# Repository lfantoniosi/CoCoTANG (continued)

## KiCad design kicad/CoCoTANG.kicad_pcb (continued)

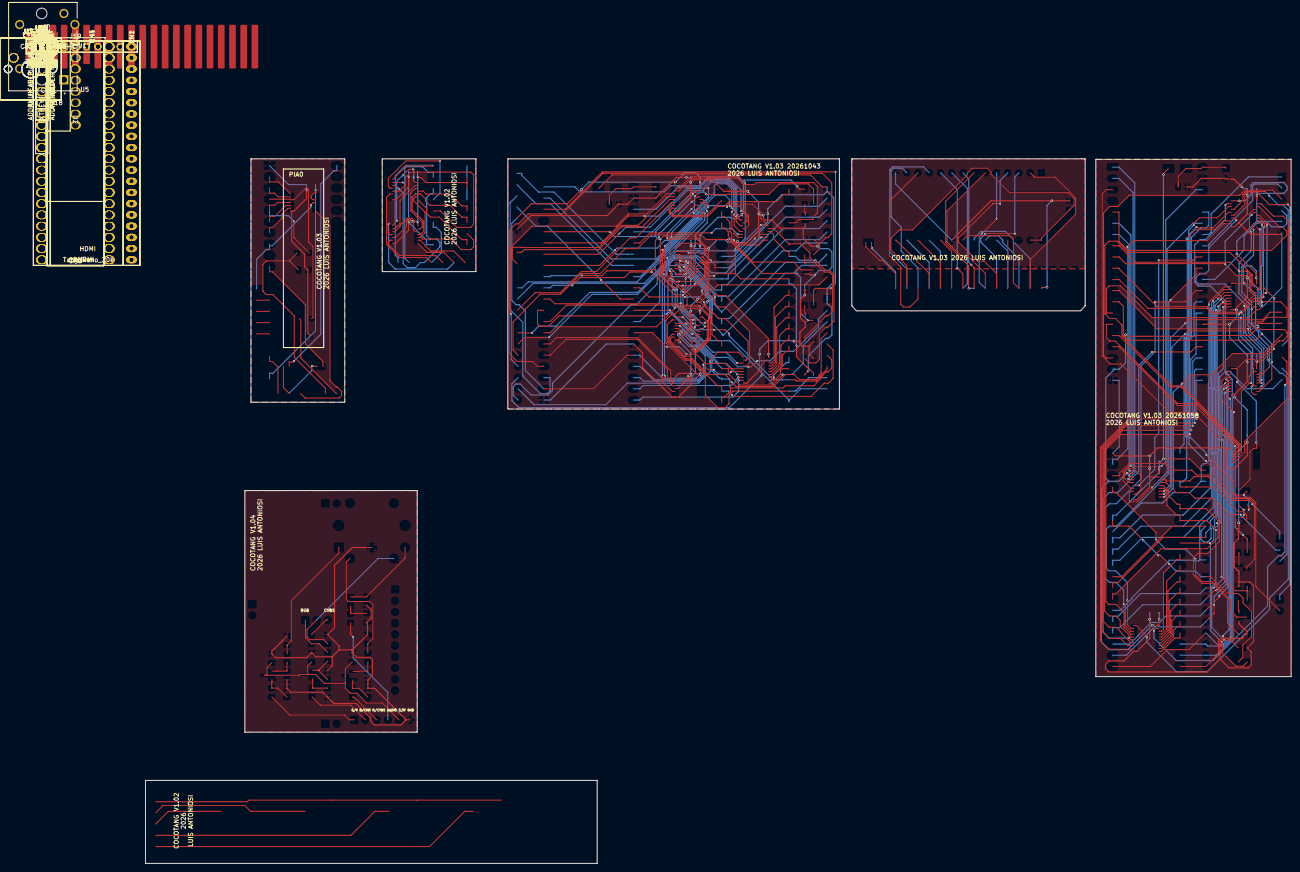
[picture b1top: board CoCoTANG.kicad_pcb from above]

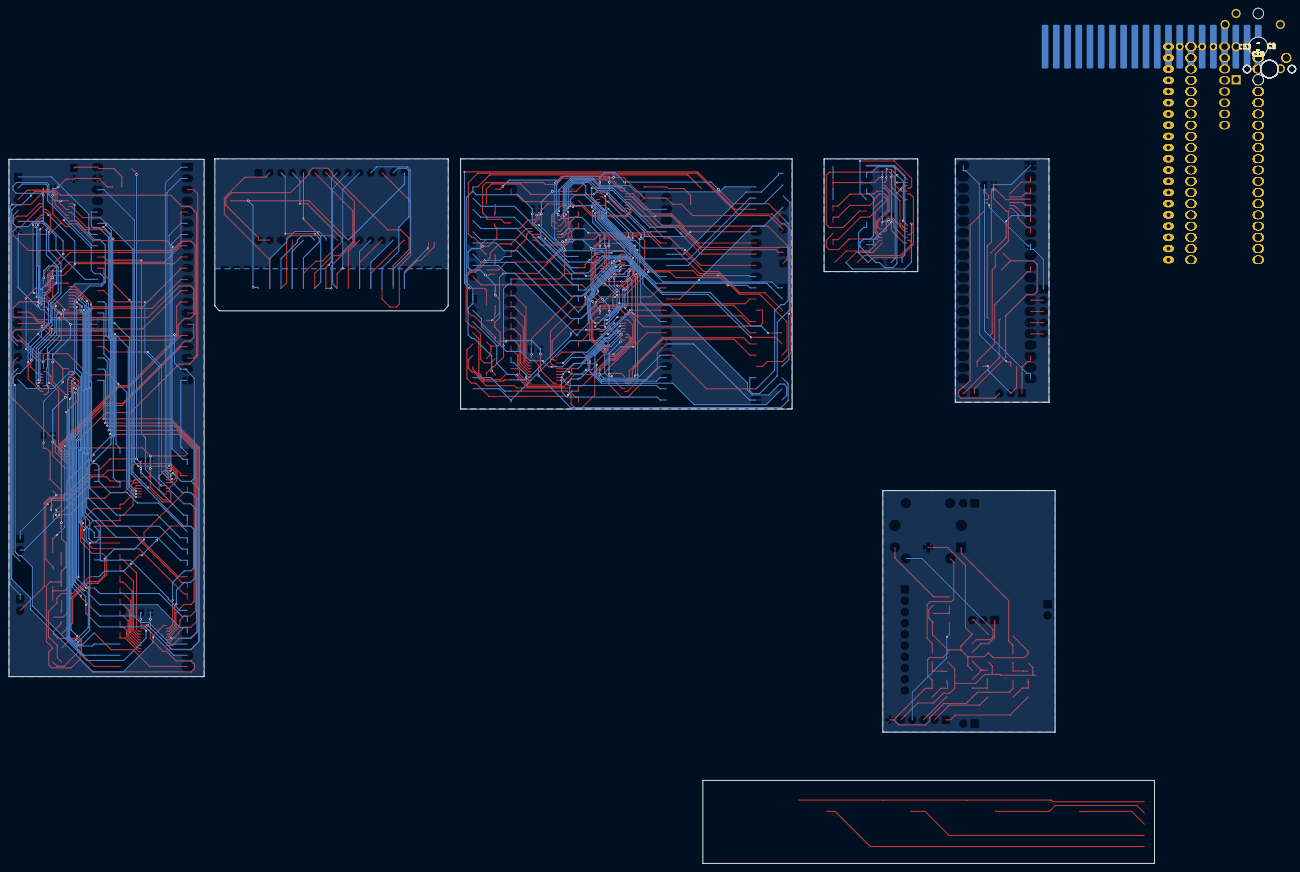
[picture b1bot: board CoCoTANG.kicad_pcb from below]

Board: 2 copper layers, 259.3 x 159.5 mm, 131 parts (15 on the bottom side), 129 nets.

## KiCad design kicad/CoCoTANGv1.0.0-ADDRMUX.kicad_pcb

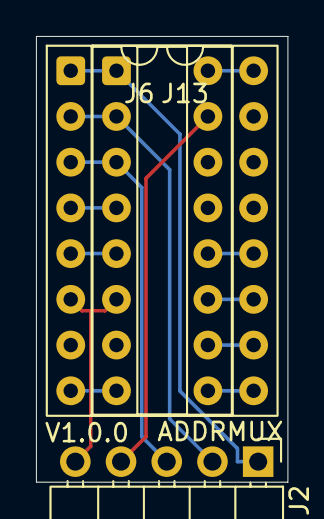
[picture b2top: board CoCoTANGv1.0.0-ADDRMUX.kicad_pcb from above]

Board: 2 copper layers, 14.0 x 24.8 mm, 3 parts (0 on the bottom side), 13 nets.

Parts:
J2: ADDRMUX; PinHeader_1x05_P2.54mm_Horizontal
J6: ADDRMUX; DIP-16_W7.62mm_Socket
J13: ADDRMUX_SOCKET; DIP-16_W7.62mm_Socket

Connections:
DP4: J6.4, J13.4
DP5: J6.5, J13.5
DP8: J6.8, J13.8
DP16: J6.16, J13.16
PIA0: J6.11, J13.11
PIA1: J6.10, J13.10
S0: J2.1, J6.1, J13.1
S1: J2.2, J6.2, J13.2
S2: J2.3, J6.3, J13.3
~CTS: J6.12, J13.12
~MRD: J2.4, J6.15
~SCS: J6.9, J13.9
~SLENB: J2.5, J6.6, J13.6

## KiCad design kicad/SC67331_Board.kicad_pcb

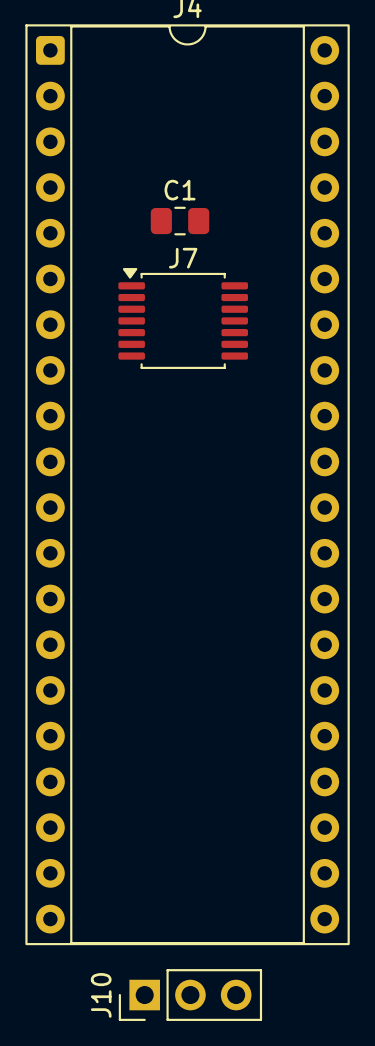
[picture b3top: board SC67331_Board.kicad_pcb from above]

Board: 2 copper layers, 4 parts (0 on the bottom side), 12 nets, no tracks yet.

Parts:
C1: 104; C_0805_2012Metric_Pad1.18x1.45mm_HandSolder
J4: SC67331; DIP-40_W15.24mm_Socket
J7: 74HC30; TSSOP-14_4.4x5mm_P0.65mm
J10: SC67331_HEADER; PinHeader_1x03_P2.54mm_Vertical

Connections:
+5V: C1.1, J4.20, J7.12, J7.14
FS: J4.18, J10.2
GND: C1.2, J4.1, J7.7
HS: J4.40, J10.1
KEYINT: J7.8, J10.3
ROW0: J4.2, J7.1
ROW1: J4.3, J7.2
ROW2: J4.4, J7.3
ROW3: J4.5, J7.4
ROW4: J4.6, J7.5
ROW5: J4.7, J7.6
ROW6: J4.8, J7.11

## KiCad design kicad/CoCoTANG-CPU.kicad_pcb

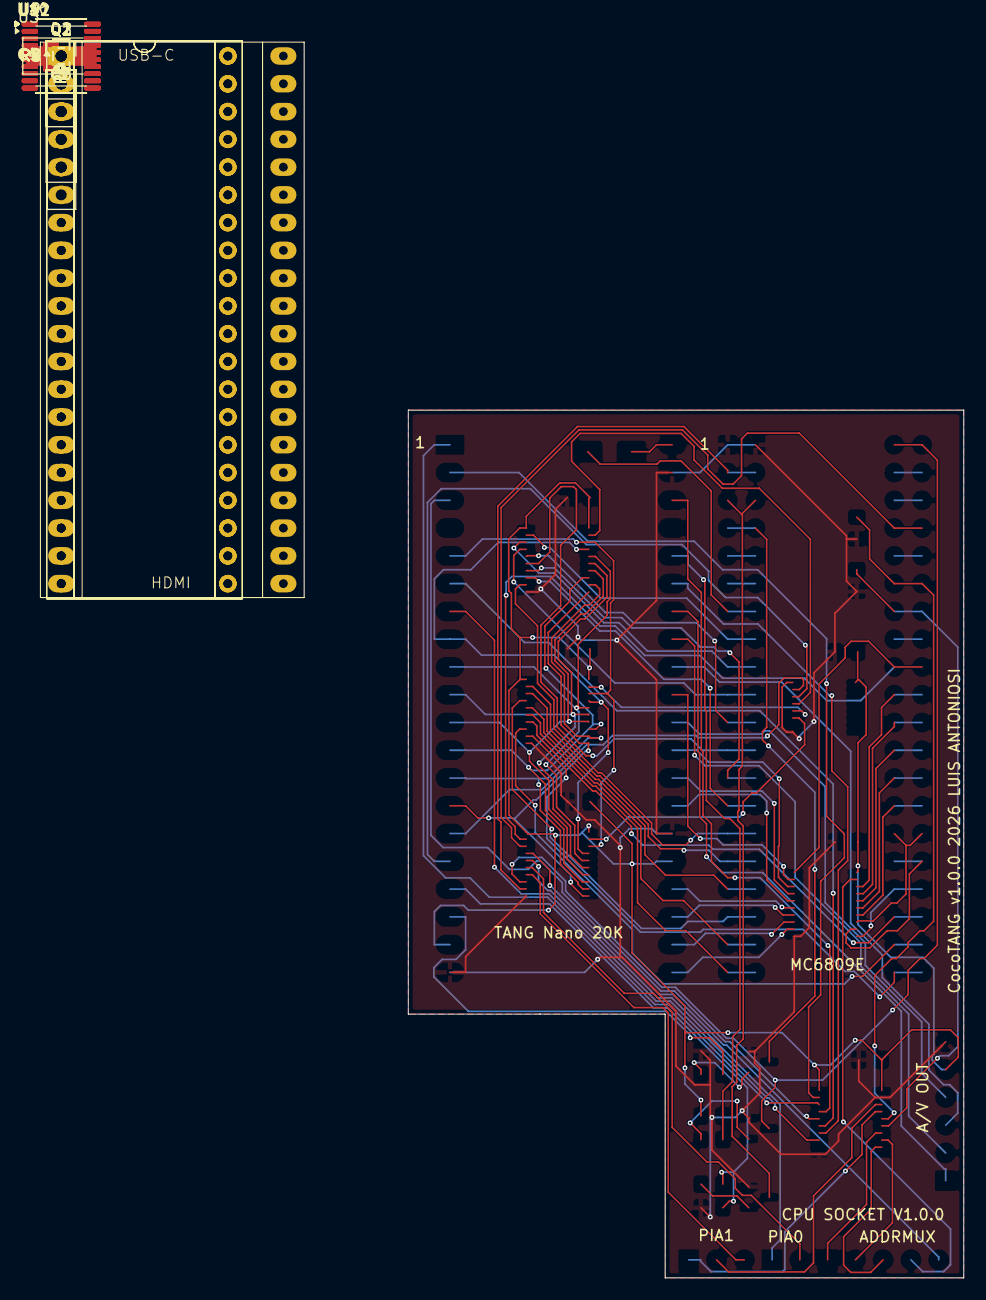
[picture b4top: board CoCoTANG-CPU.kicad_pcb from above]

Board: 2 copper layers, 50.8 x 79.4 mm, 31 parts (0 on the bottom side), 90 nets.

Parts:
C2, C3, C4, C5, C6, C7: 104; C_0805_2012Metric_Pad1.18x1.45mm_HandSolder
D2: SS14; D_SMA
J1: CPU; DIP-40_W15.24mm_Socket
J2: ADDRMUX; PinHeader_1x05_P2.54mm_Vertical
J3: CPU_SOCKET; DIP-40_W15.24mm_Socket
J7: AV_HEADER; PinSocket_1x06_P2.54mm_Vertical
J10: PIA0; PinHeader_1x03_P2.54mm_Vertical
J11: PIA1; PinHeader_1x02_P2.54mm_Vertical
Q1, Q2, Q3: 2N3904; SOT-23
R2, R4, R6: 10K; R_0805_2012Metric_Pad1.20x1.40mm_HandSolder
R3, R5, R7: 4.7K; R_0805_2012Metric_Pad1.20x1.40mm_HandSolder
R8, R9: 47K; R_0805_2012Metric_Pad1.20x1.40mm_HandSolder
U3: 74HC139; TSSOP-16_4.4x5mm_P0.65mm
U5: Tang_Nano_20k
U8, U9, U10, U11, U12: SN74LVC245AN; TSSOP-20_4.4x6.5mm_P0.65mm

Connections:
+3.3V: C2.1, C3.1, C4.1, C5.1, C6.1, C7.1, J7.5, R4.1, U3.16, U5.19 (3V3), U5.25 (3V3), U8.1 (A->B), U8.20 (VCC), U9.1 (A->B), U9.20 (VCC), U10.1 (A->B), U10.20 (VCC), U11.1 (A->B), U11.20 (VCC), U12.20 (VCC)
+5V: D2.2 (A), J1.7, J3.7
A0: J1.8, J3.8, U8.2 (A0)
A1: J1.9, J3.9, U8.3 (A1)
A2: J1.10, J3.10, U8.4 (A2)
A3: J1.11, J3.11, U8.5 (A3)
A4: J1.12, J3.12, U8.6 (A4)
A5: J1.13, J3.13, U8.7 (A5)
A6: J1.14, J3.14, U8.8 (A6)
A7: J1.15, J3.15, U8.9 (A7)
A8: J1.16, J3.16, U10.2 (A0)
A9: J1.17, J3.17, U10.3 (A1)
A10: J1.18, J3.18, U10.4 (A2)
A11: J1.19, J3.19, U10.5 (A3)
A12: J1.20, J3.20, U10.6 (A4)
A13: J1.21, J3.21, U10.9 (A7)
A14: J1.22, J3.22, U10.8 (A6)
A15: J1.23, J3.23, U10.7 (A5)
AUDIO_33: J7.4, U5.30 (55_IOR36B)
CP5: J1.5, J3.5
CP6: J1.6, J3.6
CP33: J1.33, J3.33
CP36: J1.36, J3.36
CP38: J1.38, J3.38
CP39: J1.39, J3.39
D0: J1.24, J3.24, U12.11 (B7)
D0_33: U5.21 (52_IOR39A), U12.9 (A7)
D1: J1.25, J3.25, U12.12 (B6)
D1_33: U5.22 (53_IOR38B), U12.8 (A6)
D2: J1.26, J3.26, U12.13 (B5)
D2_33: U5.23 (71_IOT44A), U12.7 (A5)
D3: J1.27, J3.27, U12.14 (B4)
D3_33: U5.24 (72_IOT40B), U12.6 (A4)
D4: J1.28, J3.28, U12.15 (B3)
D4_33: U5.27 (79_IOT27B), U12.5 (A3)
D5: J1.29, J3.29, U12.16 (B2)
D5_33: U5.28 (86_IOT4A), U12.4 (A2)
D6: J1.30, J3.30, U12.17 (B1)
D6_33: U5.29 (49_IOR49A), U12.3 (A1)
D7: J1.31, J3.31, U12.18 (B0)
D7_33: U5.31 (48_IOR49B), U12.2 (A0)
E: J1.34, J3.34, R8.1, U9.15 (B3)
E_33: U5.3 (75_IOT34A), U9.5 (A3)
FIRQ_33: R6.2, R7.2, U5.18 (18_IOL49B_LED3)
GND: C2.2, C3.2, C4.2, C5.2, C6.2, C7.2, J1.1, J3.1, J7.6, Q1.1 (E), Q2.1 (E), Q3.1 (E), R2.1, R6.1, R8.2, R9.2, U3.1, U3.8, U5.20 (GND), U5.26 (GND), U5.39 (GND), U8.10 (GND), U9.10 (GND), U9.19 (CE), U10.10 (GND), U11.10 (GND), U12.10 (GND)
HALT_33: R4.2, R5.2, U5.36 (42_IOB42B)
IRQ_33: R2.2, R3.2, U5.17 (19_IOL51A_LED4)
KEYINT: J10.3, U11.7 (A5)
MP0_33: U5.5 (77_IOT30A), U8.18 (B0), U10.18 (B0), U11.18 (B0)
MP1_33: U5.8 (27_IOB8A), U8.17 (B1), U10.17 (B1), U11.17 (B1)
MP2_33: U5.9 (28_IOB8B), U8.16 (B2), U10.16 (B2), U11.16 (B2)
MP3_33: U5.10 (25_IOB6A), U8.15 (B3), U10.15 (B3), U11.15 (B3)
MP4_33: U5.11 (26_IOB6B), U8.14 (B4), U10.14 (B4), U11.14 (B4)
MP5_33: U5.12 (29_IOB14A), U8.13 (B5), U10.13 (B5), U11.13 (B5)
MP6_33: U5.13 (30_IOB14B), U8.12 (B6), U10.12 (B6), U11.12 (B6)
MP7_33: U5.14 (31_IOB29A), U8.11 (B7), U10.11 (B7), U11.11 (B7)
MSEL0: U3.4, U8.19 (CE)
MSEL0_33: U3.2, U5.15 (17_IOL49A_LED2)
MSEL1: U3.5, U10.19 (CE)
MSEL1_33: U3.3, U5.16 (20_IOL51B_LED5)
MSEL2: U3.6, U11.19 (CE)
unnamed: D2.1 (K), U5.40 (5V)
unnamed: Q1.2 (B), R3.1
unnamed: Q2.2 (B), R5.1
unnamed: Q3.2 (B), R7.1
PB_33: J7.2, U5.33 (54_IOR38A)
PR_33: J7.3, U5.32 (51_IOR45A)
Q: J1.35, J3.35, R9.1, U9.16 (B2)
Q_33: U5.38 (78_IOT30B), U9.4 (A2)
R/~W: J1.32, J3.32, U11.2 (A0), U12.1 (A->B)
S0: J2.1, U9.14 (B4)
S0_33: U5.6 (15_IOL47A_LED0), U9.6 (A4)
S1: J2.2, U9.13 (B5)
S1_33: U5.35 (41_IOB43A), U9.7 (A5)
S2: J2.3, U9.12 (B6)
S2_33: U5.7 (16_IOL47B_LED1), U9.8 (A6)
SERNT: J11.1, U11.5 (A3)
Y_33: J7.1, U5.34 (56_IOR36A)
~CART: J11.2, U11.6 (A4)
~FIRQ: J1.4, J3.4, Q3.3 (C)
~FS_33: U5.2 (74_IOT34B), U9.2 (A0)
~FS: J10.2, U9.18 (B0)
~HALT: J1.40, J3.40, Q2.3 (C), U11.8 (A6)
~HS_33: U5.1 (73_IOT40A), U9.3 (A1)
~HS: J10.1, U9.17 (B1)
~IRQ: J1.3, J3.3, Q1.3 (C)
~MRD: J2.4, U12.19 (CE)
~NMI: J1.2, J3.2, U11.9 (A7)
~RESET: J1.37, J3.37, U11.3 (A1)
~SLENB: J2.5, U11.4 (A2)

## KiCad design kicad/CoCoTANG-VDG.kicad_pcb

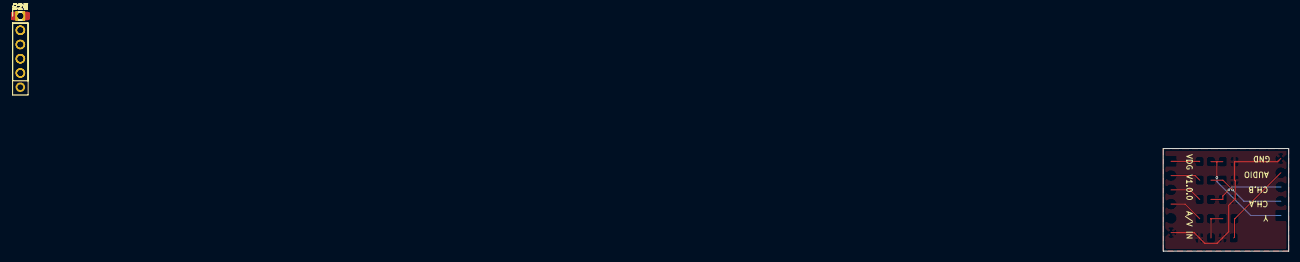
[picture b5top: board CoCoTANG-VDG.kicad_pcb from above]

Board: 2 copper layers, 22.4 x 18.3 mm, 12 parts (0 on the bottom side), 10 nets.

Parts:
C17, C18, C19: 68pF; C_0805_2012Metric_Pad1.18x1.45mm_HandSolder
C20: 4.7uF; C_0805_2012Metric_Pad1.18x1.45mm_HandSolder
C21: 6.8nF; C_0805_2012Metric_Pad1.18x1.45mm_HandSolder
J16: VDG_IN; PinHeader_1x06_P2.54mm_Vertical
J19: VDG_OUT; PinHeader_1x05_P2.54mm_Vertical
R16: 1K; R_0805_2012Metric_Pad1.20x1.40mm_HandSolder
R17: 100K; R_0805_2012Metric_Pad1.20x1.40mm_HandSolder
R19, R20, R21: 100; R_0805_2012Metric_Pad1.20x1.40mm_HandSolder

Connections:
AUDIO_33: J16.4, R16.1
AUDIO_RCA: C20.2, J19.4, R17.2
CHA_33: J16.2, R20.1
CHA_VDG: C18.1, J19.2, R20.2
CHB_33: J16.3, R21.1
CHB_VDG: C19.1, J19.3, R21.2
GND: C17.2, C18.2, C19.2, C21.1, J16.6, J19.5, R17.1
unnamed: C20.1, C21.2, R16.2
Y_33: J16.1, R19.1
Y_VDG: C17.1, J19.1, R19.2

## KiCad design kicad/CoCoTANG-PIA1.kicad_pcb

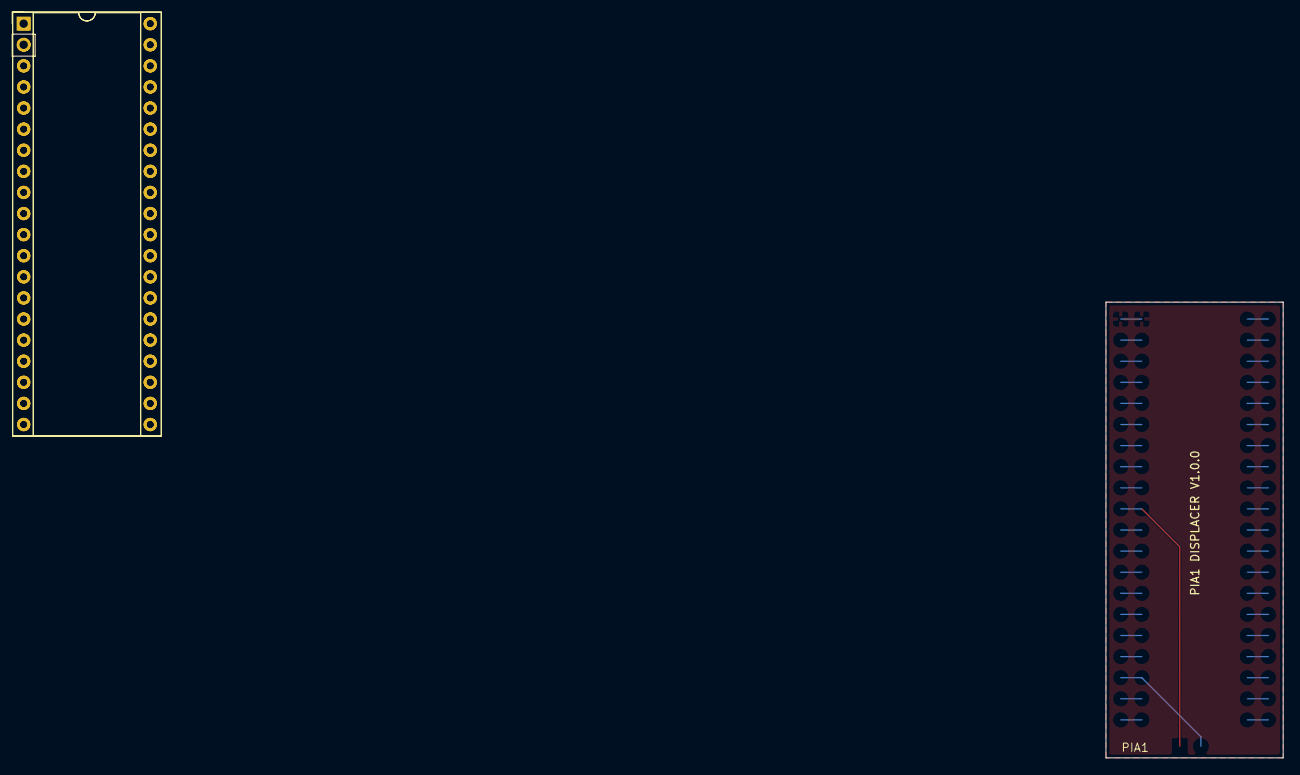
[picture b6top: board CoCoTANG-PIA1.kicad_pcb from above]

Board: 2 copper layers, 21.3 x 54.9 mm, 3 parts (0 on the bottom side), 40 nets.

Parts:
J5: PIA1; DIP-40_W15.24mm_Socket
J12: PIA1_SOCKET; DIP-40_W15.24mm_Socket
J15: PIA1; PinHeader_1x02_P2.54mm_Vertical

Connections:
+5V: J5.20, J12.20
BP2: J5.2, J12.2
BP3: J5.3, J12.3
BP4: J5.4, J12.4
BP5: J5.5, J12.5
BP6: J5.6, J12.6
BP7: J5.7, J12.7
BP8: J5.8, J12.8
BP9: J5.9, J12.9
BP11: J5.11, J12.11
BP12: J5.12, J12.12
BP13: J5.13, J12.13
BP14: J5.14, J12.14
BP15: J5.15, J12.15
BP16: J5.16, J12.16
BP17: J5.17, J12.17
BP19: J5.19, J12.19
BP21: J5.21, J12.21
BP22: J5.22, J12.22
BP23: J5.23, J12.23
BP24: J5.24, J12.24
BP25: J5.25, J12.25
BP26: J5.26, J12.26
BP27: J5.27, J12.27
BP28: J5.28, J12.28
BP29: J5.29, J12.29
BP30: J5.30, J12.30
BP31: J5.31, J12.31
BP32: J5.32, J12.32
BP33: J5.33, J12.33
BP34: J5.34, J12.34
BP35: J5.35, J12.35
BP36: J5.36, J12.36
BP37: J5.37, J12.37
BP38: J5.38, J12.38
BP39: J5.39, J12.39
BP40: J5.40, J12.40
GND: J5.1, J12.1
SERNT: J5.10, J12.10, J15.1
~CART: J5.18, J12.18, J15.2

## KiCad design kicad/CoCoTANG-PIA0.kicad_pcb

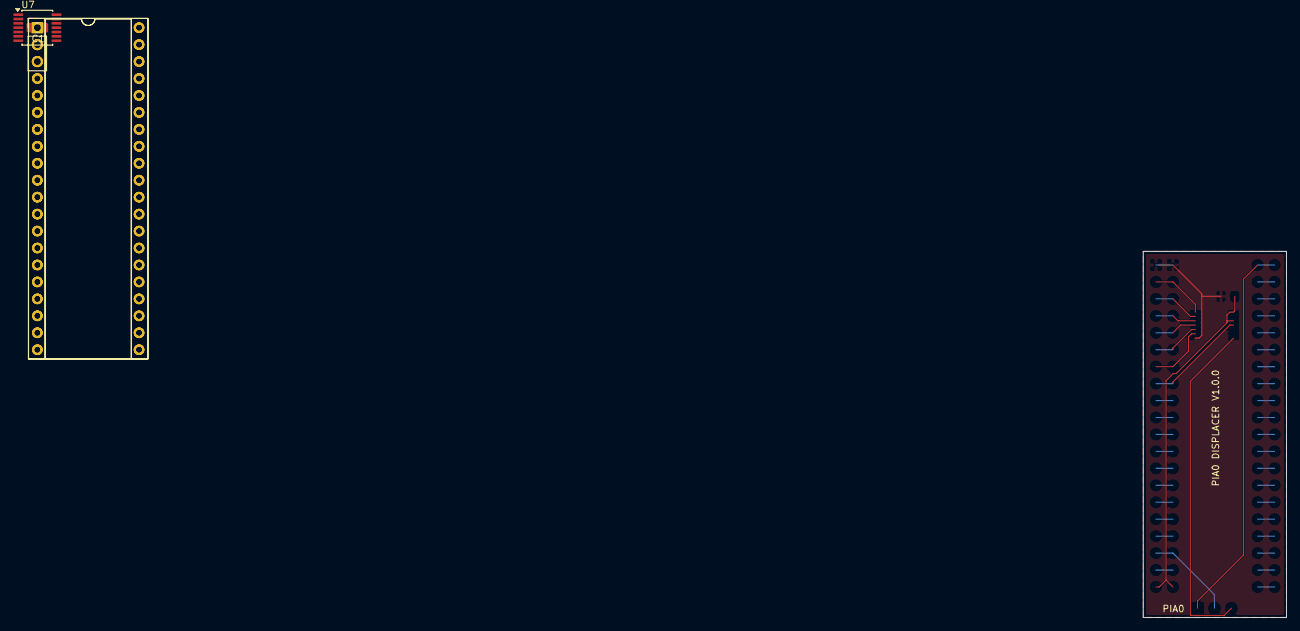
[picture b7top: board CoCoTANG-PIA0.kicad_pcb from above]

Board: 2 copper layers, 21.5 x 54.9 mm, 5 parts (0 on the bottom side), 41 nets.

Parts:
C1: 104; C_0805_2012Metric_Pad1.18x1.45mm_HandSolder
J4: PIA0; DIP-40_W15.24mm_Socket
J9: PIA0_SOCKET; DIP-40_W15.24mm_Socket
J14: PIA0; PinHeader_1x03_P2.54mm_Vertical
U7: 74HC30; TSSOP-14_4.4x5mm_P0.65mm

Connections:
+5V: C1.1, J4.20, J9.20, U7.12, U7.14
AP9: J4.9, J9.9
AP10: J4.10, J9.10
AP11: J4.11, J9.11
AP12: J4.12, J9.12
AP13: J4.13, J9.13
AP14: J4.14, J9.14
AP15: J4.15, J9.15
AP16: J4.16, J9.16
AP17: J4.17, J9.17
AP18: J4.19, J9.19
AP21: J4.21, J9.21
AP22: J4.22, J9.22
AP23: J4.23, J9.23
AP24: J4.24, J9.24
AP25: J4.25, J9.25
AP26: J4.26, J9.26
AP27: J4.27, J9.27
AP28: J4.28, J9.28
AP29: J4.29, J9.29
AP30: J4.30, J9.30
AP31: J4.31, J9.31
AP32: J4.32, J9.32
AP33: J4.33, J9.33
AP34: J4.34, J9.34
AP35: J4.35, J9.35
AP36: J4.36, J9.36
AP37: J4.37, J9.37
AP38: J4.38, J9.38
AP39: J4.39, J9.39
GND: C1.2, J4.1, J9.1, U7.7
KEYINT: J14.3, U7.8
ROW0: J4.2, J9.2, U7.1
ROW1: J4.3, J9.3, U7.2
ROW2: J4.4, J9.4, U7.3
ROW3: J4.5, J9.5, U7.4
ROW4: J4.6, J9.6, U7.5
ROW5: J4.7, J9.7, U7.6
ROW6: J4.8, J9.8, U7.11
~FS: J4.18, J9.18, J14.2
~HS: J4.40, J9.40, J14.1

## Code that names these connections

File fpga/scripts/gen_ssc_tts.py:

#!/usr/bin/env python3
"""Compile the public NRL English rules to the SSC's bytecode ROM.

Context alternatives are expanded without changing rule priority. # and :
compile to character classes and backtracking zero-or-more instructions.
The generated ROM is synchronous so Gowin can map it into block memory.
"""
import itertools
import json
import re
from pathlib import Path

ROOT = Path(__file__).resolve().parent.parent
DATA = ROOT / 'src/third_party/nrl_tts'
ALLOPHONES = ('PA1 PA2 PA3 PA4 PA5 OY AY EH KK3 PP JH NN1 IH TT2 RR1 AX '
              'MM TT1 DH1 IY EY DD1 UW1 AO AA YY2 AE HH1 BB1 TH UH UW2 '
              'AW DD2 GG3 VV GG1 SH ZH RR2 FF KK2 KK1 ZZ NG LL WW XR '
              'WH YY1 CH ER1 ER2 OW DH2 SS NN2 HH2 OR AR YR GG2 EL BB2').split()
CODES = {name: i for i, name in enumerate(ALLOPHONES)}
CLASSES = {'#': [128, 132], '^': [129], '.': [130], '+': [131], ':': [133]}
ALTERNATIVES = {'%': ['ER', 'E', 'ES', 'ED', 'ING', 'ELY'],
                '&': ['S', 'C', 'G', 'Z', 'X', 'J', 'CH', 'SH'],
                '@': ['T', 'S', 'R', 'D', 'L', 'Z', 'N', 'J', 'TH', 'CH', 'SH']}


def contexts(pattern, reverse=False):
    items = [ALTERNATIVES.get(c, [c]) for c in pattern]
    for parts in itertools.product(*items):
        expanded = ''.join(parts)
        if reverse:
            expanded = expanded[::-1]
        yield [b for c in expanded for b in CLASSES.get(c, [ord(c)])]


def compile_rules():
    source = json.loads((DATA / 'eng_to_ipa.json').read_text())
    mapping = json.loads((DATA / 'ipa_to_sp0256.json').read_text())
    phonemes = {}
    for name, rules in mapping.items():
        if name != 'PUNCT':
            phonemes[name] = rules[0].split('=')[1].strip('[]').split()
    phonemes.update({'< >': ['PA3'], '<,>': ['PA4'], '<.>': ['PA5'],
                     '<?>': ['PA5'], '<->': ['PA4']})
    rom = [0]  # address zero means no more rules
    groups = {}
    for group, lines in source.items():
        records = []
        for line in lines:
            left, body, right, output = re.fullmatch(r'(.*?)\[(.*?)\](.*?)=(.*)', line).groups()
            result = []
            for fragment in re.findall(r'/([^/]*)/', output):
                if fragment.strip():
                    for phoneme in ([fragment] if fragment.startswith('<') else fragment.split()):
                        result.extend(CODES[x] for x in phonemes[phoneme])
            assert body, line
            for pre, post in itertools.product(contexts(left, True), contexts(right)):
                assert sum(x in (132, 133) for x in pre) <= 4, line
                assert sum(x in (132, 133) for x in post) <= 4, line
                records.append(list(body.encode('ascii')) + [0] + pre + [0] + post + [0] + result + [255])
        groups[group] = len(rom)
        for i, record in enumerate(records):
            following = len(rom) + 2 + len(record) if i + 1 < len(records) else 0
            rom.extend([following & 255, following >> 8] + record)
    assert len(rom) <= 8192, len(rom)
    return rom, groups


def render():
    rom, groups = compile_rules()
    start = {ord(c): groups[c] for c in 'ABCDEFGHIJKLMNOPQRSTUVWXYZ'}
    start.update({ord(c): groups['NUMBER'] for c in '0123456789'})
    start.update({ord(c): groups['PUNCT'] for c in " '-,.?"})
    text = '''// Generated by scripts/gen_ssc_tts.py from the public NRL rules.
// See src/third_party/nrl_tts/LICENSE and README.md for provenance.
module coco_ssc_tts_rom (
    input clk,input [12:0] address,output reg [7:0] data,
    input [7:0] letter,output reg [12:0] first_rule
);
    (* syn_romstyle = "block_rom" *) reg [7:0] rom [0:8191];
    initial begin
'''
    text += ''.join(f"        rom[{i}]=8'd{b};\n" for i, b in enumerate(rom))
    text += '''    end
    always @(posedge clk) data<=rom[address];
    always @* begin
        case(letter)
'''
    text += ''.join(f"            8'd{k}: first_rule=13'd{v};\n" for k, v in sorted(start.items()))
    text += '''            default: first_rule=0;
        endcase
    end
endmodule
'''
    return text, len(rom)


if __name__ == '__main__':
    text, size = render()
    (ROOT / 'src/audio/coco_ssc_tts_rom.v').write_text(text)
    print(f'SSC pronunciation ROM: {size}/8192 bytes')
